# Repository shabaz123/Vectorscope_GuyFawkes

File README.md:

# Vectorscope_GuyFawkes

A reimplementation of the Vectorscope from https://github.com/Hack-a-Day/Vectorscope

This version is simply called Vectorscope_GuyFawkes for no other reason other than to identify it from the various other implementations, since it was created on a November.

This version was created using KiCad without importing any schematic or PCB or Gerber files, since I didn't know of a way to do that. No guarantee it will work!

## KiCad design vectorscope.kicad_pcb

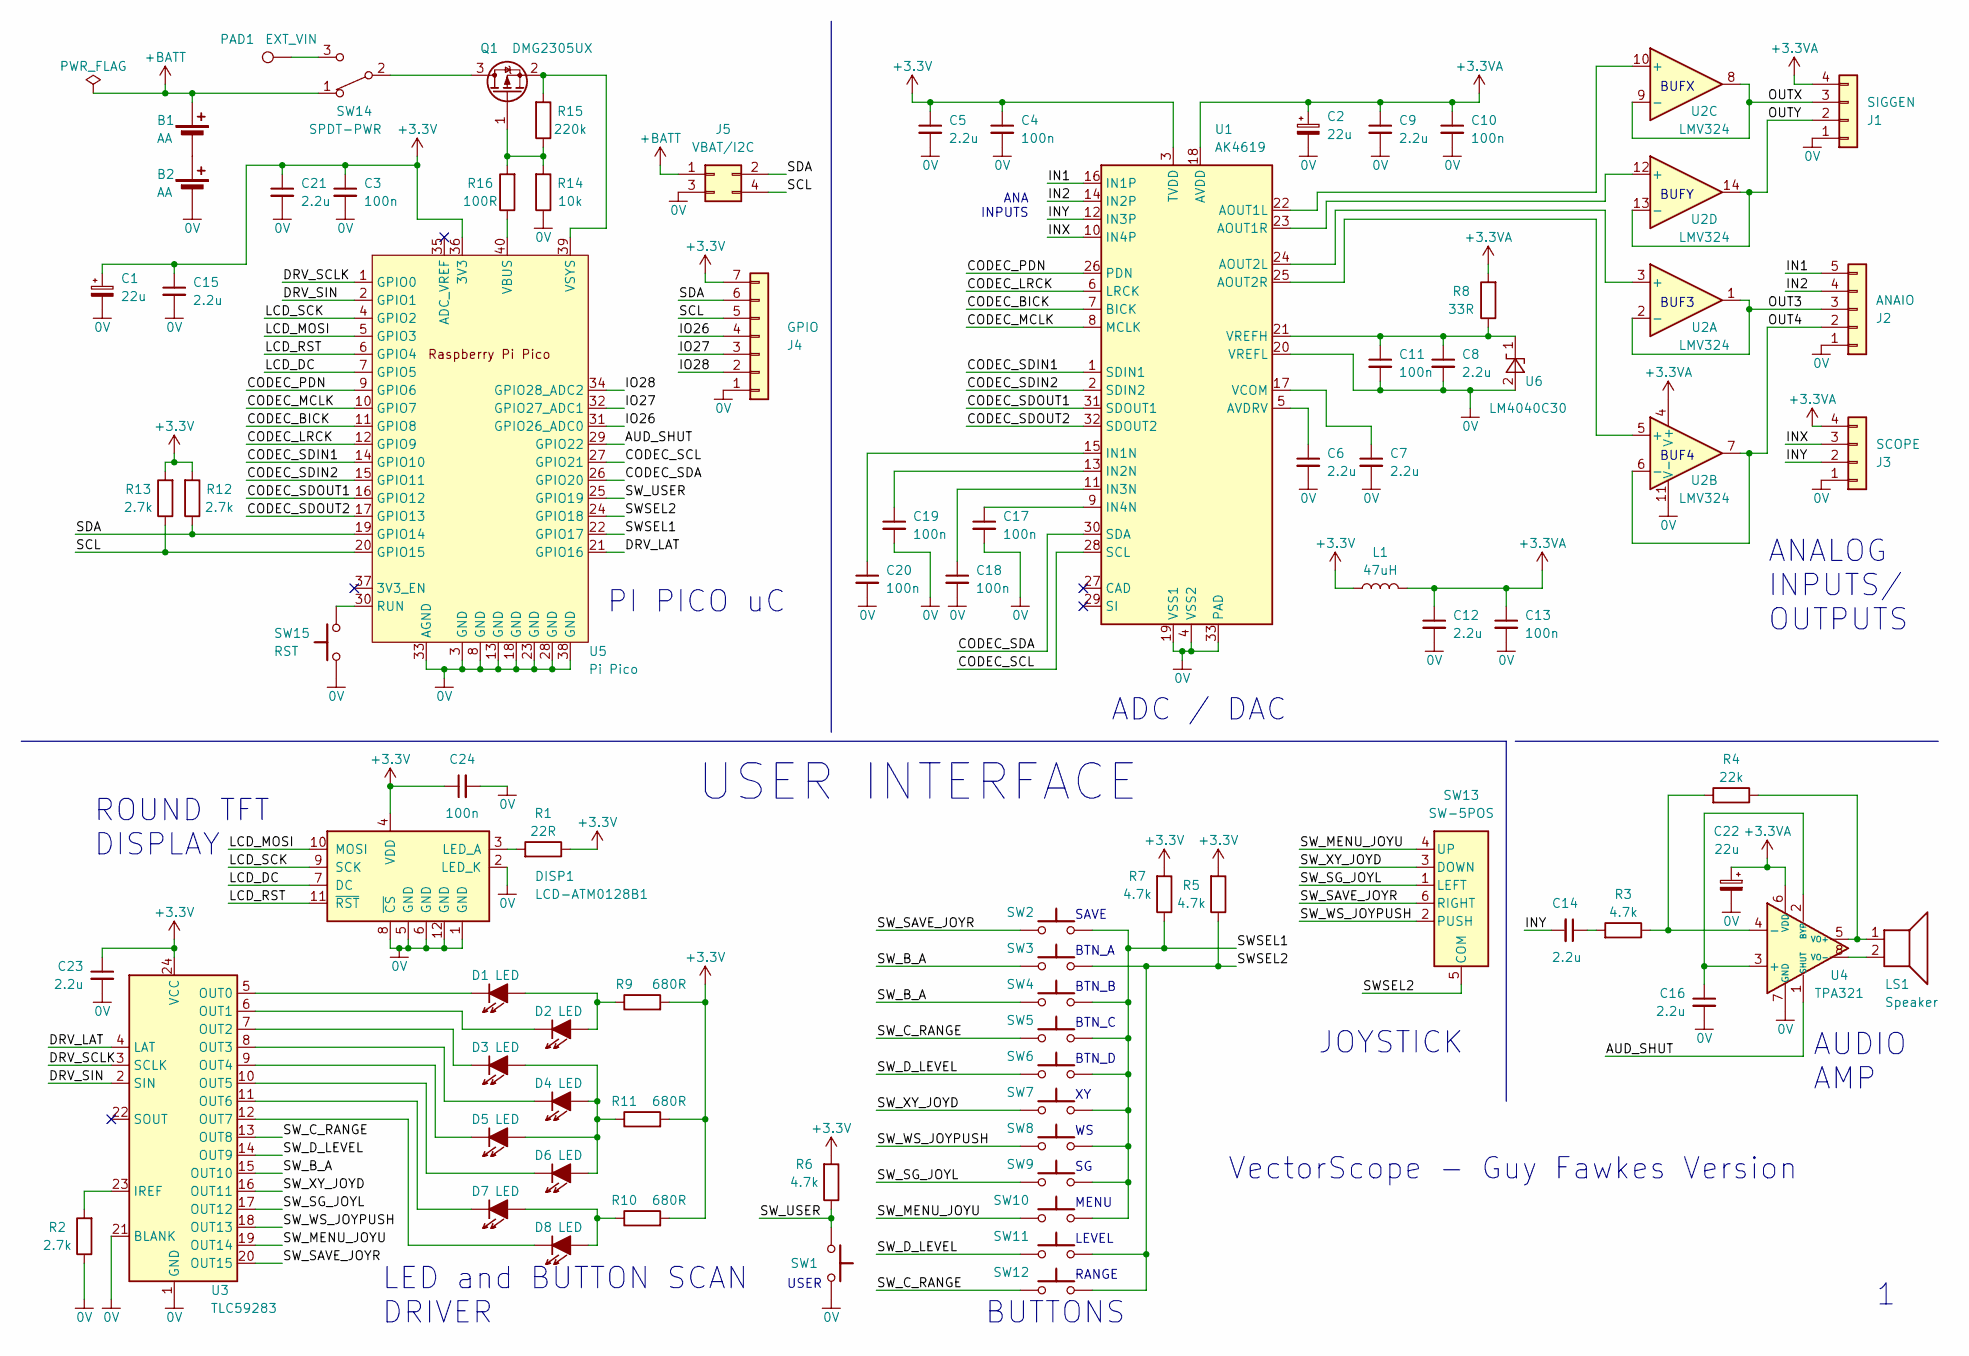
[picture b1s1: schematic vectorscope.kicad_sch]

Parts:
B1, B2: AA; AA-holder-keystone-2460
C1, C2, C22: 22u; Cap-Tant-CaseB
C3, C4, C10, C11, C13, C17, C18, C19, C20, C24: 100n; C_0603_1608Metric_Pad1.08x0.95mm_HandSolder
C5, C6, C7, C8, C9, C12, C14, C15, C16, C21, C23: 2.2u; C_0603_1608Metric_Pad1.08x0.95mm_HandSolder
D1, D2, D3, D4, D5, D6, D7, D8: LED; LED_2_1.25
DISP1: LCD-ATM0128B1
J1: SIGGEN; PinHeader1x4-2.54mm-NoSilk
J2: ANAIO; PinHeader1x5-2.54mm-NoSilk
J3: SCOPE; PinHeader1x4-2.54mm-NoSilk
J4: GPIO; PinHeader1x7-2.54mm-NoSilk
J5: VBAT/I2C; PinHeader2x2-2.54mm-NoSilk
L1: 47uH; L_0805_2012Metric_Pad1.15x1.40mm_HandSolder
LS1: Speaker; Speaker-Pads
PAD1: EXT_VIN; Terminal-Single-Hole-1mm
Q1: DMG2305UX; SOT-23
R1: 22R; R_0805_2012Metric_Pad1.20x1.40mm_HandSolder
R2, R12, R13: 2.7k; R_0805_2012Metric_Pad1.20x1.40mm_HandSolder
R3, R5, R6, R7: 4.7k; R_0805_2012Metric_Pad1.20x1.40mm_HandSolder
R4: 22k; R_0805_2012Metric_Pad1.20x1.40mm_HandSolder
R8: 33R; R_0805_2012Metric_Pad1.20x1.40mm_HandSolder
R9, R10, R11: 680R; R_0805_2012Metric_Pad1.20x1.40mm_HandSolder
R14: 10k; R_0805_2012Metric_Pad1.20x1.40mm_HandSolder
R15: 220k; R_0805_2012Metric_Pad1.20x1.40mm_HandSolder
R16: 100R; R_0805_2012Metric_Pad1.20x1.40mm_HandSolder
SW1, SW2, SW3, SW4, SW5, SW6, SW7, SW8, SW9: PTS645S-TACT-6mm-SMT; Tact-SW-6mm-PTS645S-SMT-G
SW10, SW11, SW12: PUSH-SWITCH-12mm; Tact-SW-12mm-TL3300-SMT
SW13: SW-5POS; Switch-Joystick-2425755-1
SW14: SPDT-PWR; SW_E-Switch_EG1218_SPDT
SW15: RST; Tact-SW-4x3mm-body
U1: AK4619; QFN-32-EP-AK
U2: LMV324; TSSOP-14_4.4bodyx5mm_P0.65mm
U3: TLC59283; SSOP24-DBQ-TI
U4: TPA321; SOIC-8
U5: Pi Pico; pi-pico-smd
U6: LM4040C30; SOT-23

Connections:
0V: B2.2 (-), C1.2, C2.2, C3.2, C4.2, C5.2, C6.2, C7.2, C8.2, C9.2, C10.2, C11.2, C12.2, C13.2, C15.2, C16.2, C17.2, C18.2, C19.2, C20.2, C21.2, C22.2, C23.2, C24.2, DISP1.1 (GND), DISP1.2 (LED_K), DISP1.5 (GND), DISP1.6 (GND), DISP1.8 (~CS), DISP1.12 (GND), J1.1, J2.1, J3.1, J4.1, J5.3, R2.1, R14.1, SW1.2, SW15.1, U1.4 (VSS2), U1.19 (VSS1), U1.20 (VREFL), U1.33 (PAD), U2.11 (V-), U3.1 (GND), U3.21 (BLANK), U4.7 (GND), U5.3 (GND), U5.8 (GND), U5.13 (GND), U5.18 (GND), U5.23 (GND), U5.28 (GND), U5.33 (AGND), U5.38 (GND), U6.2 (A)
+3.3V: C1.1, C3.1, C4.1, C5.1, C15.1, C21.1, C23.1, C24.1, DISP1.4 (VDD), J4.7, L1.1, R1.1, R5.2, R6.2, R7.2, R9.2, R10.2, R11.2, R12.2, R13.2, U1.3 (TVDD), U3.24 (VCC), U5.36 (3V3)
+3.3VA: C2.1, C9.1, C10.1, C12.1, C13.1, C22.1, J1.4, J3.4, L1.2, R8.2, U1.18 (AVDD), U2.4 (V+), U4.6 (VDD)
+BATT: B1.1 (+), J5.1, SW14.1 (A)
/AUD_SHUT: U4.1 (SHUT), U5.29 (GPIO22)
/CODEC_BICK: U1.7 (BICK), U5.11 (GPIO8)
/CODEC_LRCK: U1.6 (LRCK), U5.12 (GPIO9)
/CODEC_MCLK: U1.8 (MCLK), U5.10 (GPIO7)
/CODEC_PDN: U1.26 (PDN), U5.9 (GPIO6)
/CODEC_SCL: U1.28 (SCL), U5.27 (GPIO21)
/CODEC_SDA: U1.30 (SDA), U5.26 (GPIO20)
/CODEC_SDIN1: U1.1 (SDIN1), U5.14 (GPIO10)
/CODEC_SDIN2: U1.2 (SDIN2), U5.15 (GPIO11)
/CODEC_SDOUT1: U1.31 (SDOUT1), U5.16 (GPIO12)
/CODEC_SDOUT2: U1.32 (SDOUT2), U5.17 (GPIO13)
/DRV_LAT: U3.4 (LAT), U5.21 (GPIO16)
/DRV_SCLK: U3.3 (SCLK), U5.1 (GPIO0)
/DRV_SIN: U3.2 (SIN), U5.2 (GPIO1)
/IN1: J2.5, U1.16 (IN1P)
/IN2: J2.4, U1.14 (IN2P)
/INX: J3.3, U1.10 (IN4P)
/INY: C14.2, J3.2, U1.12 (IN3P)
/IO26: J4.4, U5.31 (GPIO26_ADC0)
/IO27: J4.3, U5.32 (GPIO27_ADC1)
/IO28: J4.2, U5.34 (GPIO28_ADC2)
/LCD_DC: DISP1.7 (DC), U5.7 (GPIO5)
/LCD_MOSI: DISP1.10 (MOSI), U5.5 (GPIO3)
/LCD_RST: DISP1.11 (~RST), U5.6 (GPIO4)
/LCD_SCK: DISP1.9 (SCK), U5.4 (GPIO2)
/OUT3: J2.3, U2.1, U2.2 (-)
/OUT4: J2.2, U2.6 (-), U2.7
/OUTX: J1.3, U2.8, U2.9 (-)
/OUTY: J1.2, U2.13 (-), U2.14
/SCL: J4.5, J5.4, R13.1, U5.20 (GPIO15)
/SDA: J4.6, J5.2, R12.1, U5.19 (GPIO14)
/SWSEL1: R7.1, SW2.2, SW4.2, SW5.2, SW6.2, SW7.2, SW8.2, SW9.2, SW10.2, U5.22 (GPIO17)
/SWSEL2: R5.1, SW3.2, SW11.2, SW12.2, SW13.5 (COM), U5.24 (GPIO18)
/SW_B_A: SW3.1, SW4.1, U3.15 (OUT10)
/SW_C_RANGE: SW5.1, SW12.1, U3.13 (OUT8)
/SW_D_LEVEL: SW6.1, SW11.1, U3.14 (OUT9)
/SW_MENU_JOYU: SW10.1, SW13.4 (UP), U3.19 (OUT14)
/SW_SAVE_JOYR: SW2.1, SW13.6 (RIGHT), U3.20 (OUT15)
/SW_SG_JOYL: SW9.1, SW13.1 (LEFT), U3.17 (OUT12)
/SW_USER: R6.1, SW1.1, U5.25 (GPIO19)
/SW_WS_JOYPUSH: SW8.1, SW13.2 (PUSH), U3.18 (OUT13)
/SW_XY_JOYD: SW7.1, SW13.3 (DOWN), U3.16 (OUT11)
unnamed: B1.2 (-), B2.1 (+)
unnamed: C14.1, R3.2
unnamed: D1.2 (A), D2.2 (A), R9.1
unnamed: D1.1 (K), U3.5 (OUT0)
unnamed: D2.1 (K), U3.6 (OUT1)
unnamed: D3.2 (A), D4.2 (A), D5.2 (A), D6.2 (A), R11.1
unnamed: D3.1 (K), U3.7 (OUT2)
unnamed: D4.1 (K), U3.8 (OUT3)
unnamed: D5.1 (K), U3.9 (OUT4)
unnamed: D6.1 (K), U3.10 (OUT5)
unnamed: D7.2 (A), D8.2 (A), R10.1
unnamed: D7.1 (K), U3.11 (OUT6)
unnamed: D8.1 (K), U3.12 (OUT7)
unnamed: DISP1.3 (LED_A), R1.2
unnamed: Q1.3 (D), SW14.2 (B)
unnamed: Q1.1 (G), R14.2, R15.1, R16.2
unnamed: Q1.2 (S), R15.2, U5.39 (VSYS)
unnamed: PAD1.1, SW14.3 (C)
unnamed: U1.22 (AOUT1L), U2.10 (+)
unnamed: U1.23 (AOUT1R), U2.12 (+)
unnamed: U1.24 (AOUT2L), U2.3 (+)
unnamed: U1.25 (AOUT2R), U2.5 (+)
unnamed: C6.1, U1.5 (AVDRV)
unnamed: C20.1, U1.15 (IN1N)
unnamed: C19.1, U1.13 (IN2N)
unnamed: C18.1, U1.11 (IN3N)
unnamed: C17.1, U1.9 (IN4N)
unnamed: C7.1, U1.17 (VCOM)
unnamed: C8.1, C11.1, R8.1, U1.21 (VREFH), U6.1 (K)
unnamed: R2.2, U3.23 (IREF)
unnamed: C16.1, U4.2 (BYP), U4.3 (+)
unnamed: R3.1, R4.2, U4.4 (-)
unnamed: LS1.1, R4.1, U4.5 (VO+)
unnamed: LS1.2, U4.8 (VO-)
unnamed: SW15.2, U5.30 (RUN)
unnamed: R16.1, U5.40 (VBUS)

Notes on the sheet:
BTN_C
ANALOG INPUTS/ OUTPUTS
BTN_B
ADC / DAC
BUFX
SAVE
BUF4
BUF3
JOYSTICK
BUTTONS
MENU
LED and BUTTON SCAN DRIVER
VectorScope - Guy Fawkes Version
BTN_D
USER INTERFACE
LEVEL
BUFY
PI PICO uC
USER
RANGE
ROUND TFT DISPLAY
AUDIO AMP
ANA INPUTS
BTN_A

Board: 2 copper layers, 81 parts (0 on the bottom side), 82 nets, no tracks yet.
